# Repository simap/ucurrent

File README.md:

µCurrent
------------------

Based entirely on [µCurrent by David Jones at EEVBlog](https://www.eevblog.com/projects/ucurrent/). 

µCurrent allows accurate measurement of micro and nano amps with a low burden voltage by outputting one millivolt per micro/nano amp. See the link above for all kinds of awesome if you want to know more.

This is a slightly simplified variation on µCurrent that allows for measuring micro and nano amps only. I used DPST switches and remove the milli amp measurement and the battery test (I can just probe the battery). The board is layed out for single sided home PCB manufacuring. I used a few through hole resistors for the non precision components to avoid extra jumpers. 

I've included a 3D printed case as well. Just melt the tabs down once the PCB is in place.

Neat Stuff
----------------

The crazy thing is that you can measure very low current things, for example an LED will generate current! I got about 160na when pointed at an indoor light. My project running on a PIC10LF320 in sleep mode is using only 560na. Cool!

You can also hook this up to a scope for even more sensitive measurements and detail. The amplifier used is very accurate and low noise.

Parts List
--------------

Part | precision | size | qty
---- | ----------| ---  | ----
100R | 5%        | 1/4w | 3
100K | 1%        | 0805 | 2
1K   | 0.1%      | 0805 | 1
75K  | 0.1%      | 0805 | 1
24K  | 0.1%      | 0805 | 1
10K  | 0.1%      | 0805 | 1
10R  | 0.1%      | 0805 | 1
100nF Capacitor|         | 0805 | 3
SPDT Slide Switch|  | PCB .1" | 2
Lithium Battery | | CR2032 |1
SMT Battery holder [mouser part](http://www.mouser.com/ProductDetail/Linx-Technologies/BAT-HLD-001/) | | 20mm| 1
MAX4239ASA+ Opamp|  | SO8 | 1 
LMV321AS5X Opamp |  | SOT23-5 | 1

I used some springs I scavenged from some old RadioShack learn electronics kits instead of banana jacks or binding posts.

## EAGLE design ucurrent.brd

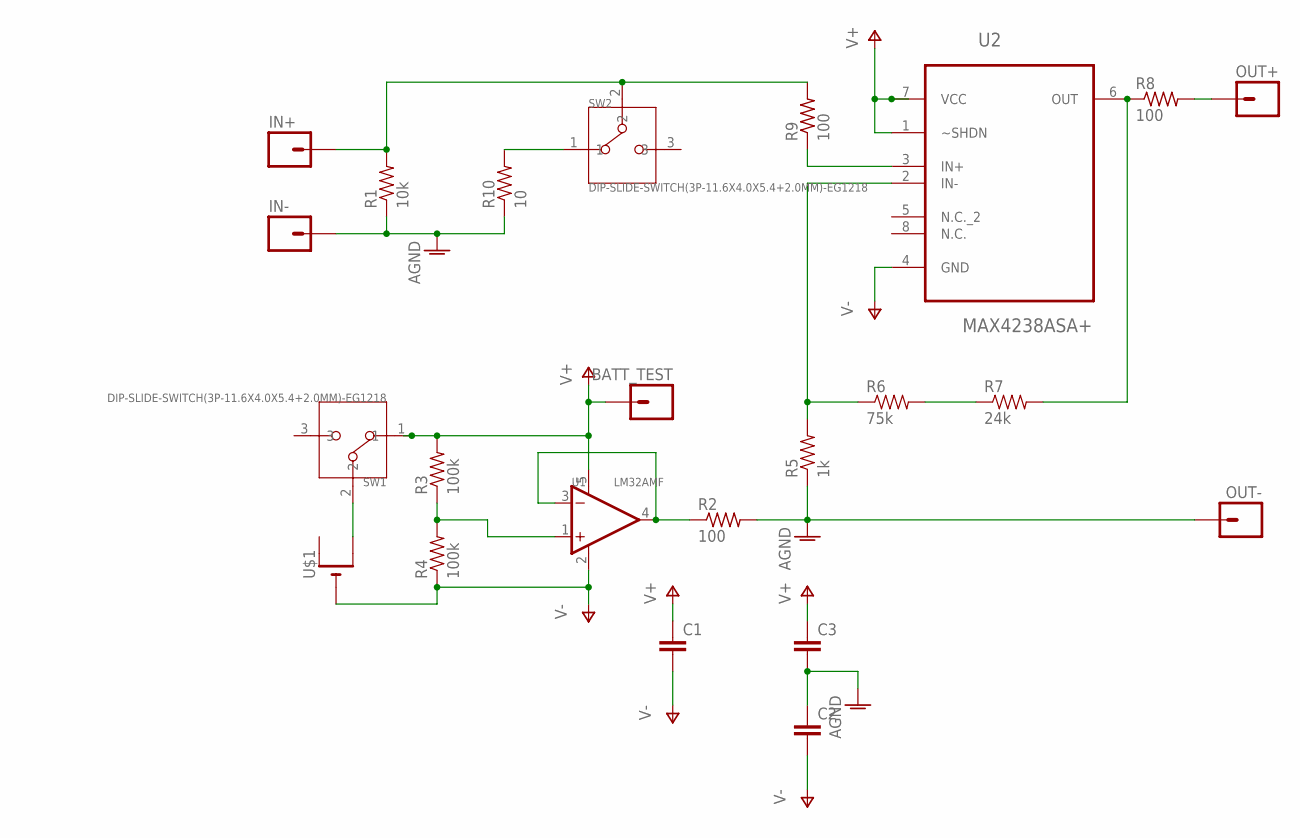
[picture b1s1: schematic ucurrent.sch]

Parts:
BATT_TEST: M01PTH_LONGPAD; 1X01_LONGPAD
C1, C2, C3: CAP0805; 0805
IN+: M01PTH_LONGPAD; 1X01_LONGPAD
IN-: M01PTH_LONGPAD; 1X01_LONGPAD
OUT+: M01PTH_LONGPAD; 1X01_LONGPAD
OUT-: M01PTH_LONGPAD; 1X01_LONGPAD
R1: 10k; 0805
R2, R8, R9: 100; 0204/7
R3, R4: 100k; 0805
R5: 1k; 0805
R6: 75k; 0805
R7: 24k; 0805
R10: 10; 0805
SW1, SW2: DIP-SLIDE-SWITCH(3P-11.6X4.0X5.4+2.0MM)-EG1218; SW3-2.5-11.6X4.0X5.4+2.0MM
U1: LM32AMF; SOT-23-5
U2: MAX4238ASA+; SOIC127P600X175-8N
U$1: CR2032SMT; CR2032-SMD

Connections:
AGND: C2.1, C3.2, IN-.1, OUT-.1, R1.1, R2.2, R5.1, R10.1
BAT+: SW1.2, U$1.+$2 (+1)
IN+: IN+.1, R1.2, R9.2, SW2.2
unnamed: R3.1, R4.2, U1.1 (IN+)
unnamed: R9.1, U2.3 (IN+)
unnamed: R7.2, R8.1, U2.6 (OUT)
unnamed: R6.2, R7.1
unnamed: R5.2, R6.1, U2.2 (IN-)
unnamed: R2.1, U1.3 (IN-), U1.4 (OUT)
unnamed: R10.2, SW2.1
OUT+: OUT+.1, R8.2
V+: BATT_TEST.1, C1.1, C3.1, R3.2, SW1.1, U1.5 (V+), U2.1 (~SHDN), U2.7 (VCC)
V-: C1.2, C2.2, R4.1, U1.2 (V-), U2.4 (GND), U$1.-

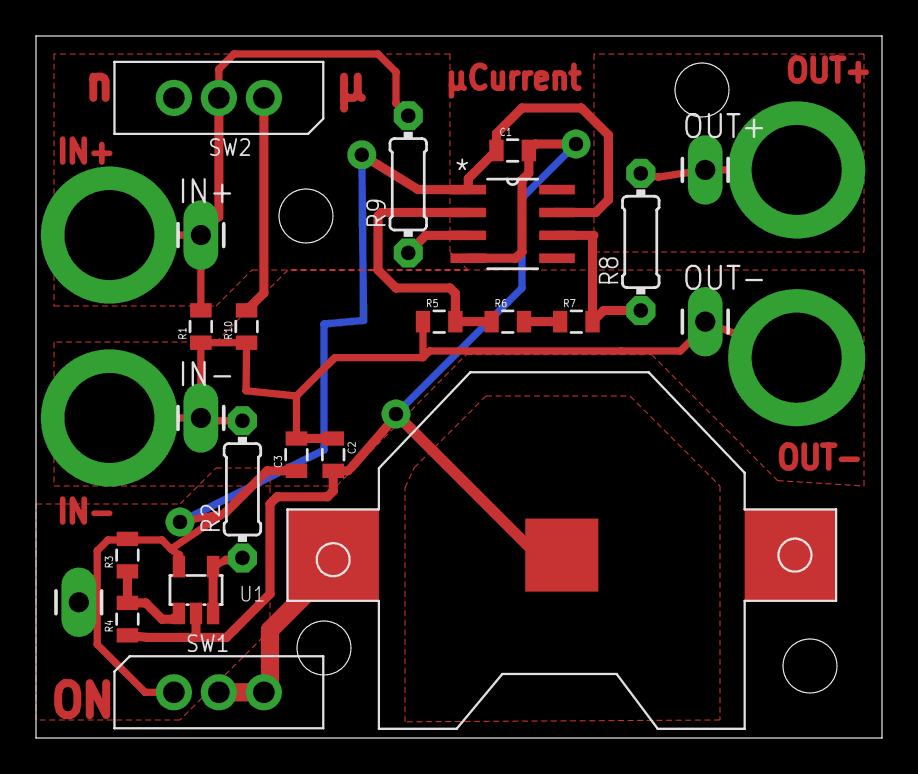
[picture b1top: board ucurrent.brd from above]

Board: 2 copper layers, 47.0 x 39.0 mm, 23 parts (0 on the bottom side), 13 nets.

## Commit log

2016-06-16 initial files

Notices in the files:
parts and their libraries:
SparkFun-Passives: Licensing: Creative Commons ShareAlike 4.0 International - https://creativecommons.org/licenses/by-sa/4.0
